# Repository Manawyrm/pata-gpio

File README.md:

pata-gpio
=============================

### Overview

**DISCLAIMER: This driver was developed for fun and learning ATA internals. If you're looking for a practical way to use PATA devices, look for commercial USB adapters.**  

pata-gpio is a Linux kernel driver for GPIO bitbanged PATA (also known as ATA/ATAPI or IDE).  
Pin configuration can be set via device tree, the regular ATA framework is used.  
  
IDE Primary/Secondary device support is implemented.  
  
### Performance

On a Raspberry Pi 4 (with direct GPIO) about **800 KiB/s reading, 500 KiB/s writing speed** is possible.
Most of the performance bottleneck is down to the usage of libgpiod (kernel gpio abstraction), 
which is optimized for tasks like switching LEDs. Data transmission is well outside the design scope of libgpiod. 
  
DMA and interrupts are not implemented at the moment.  
  
### Device tree configuration

Pin configuration can be specified in the device tree.  
An example device tree is provided as [atapi-direct.dts](https://github.com/Manawyrm/pata-gpio/blob/master/atapi-direct.dts).  
This includes the pin configuration for the schematic linked at the bottom of this readme.  
  
The following device tree properties are present:  

| Property      | Usage         | Required  |
| ------------- |-------------| -----|
| `databus-gpios`      | list of 16 GPIO pins, connected to ATA D0 - D15 in this order | yes |
| `cs-gpios`      | list of 2 GPIO pins, connected to ATA CS0 and CS1 in this order      | yes |
| `address-gpios` | list of 3 GPIO pins, connected to ATA DA0, DA1 and DA2 in this order  | yes |
| `strobe-write-gpio`      | GPIO pin, connected to ATA IOW line | yes |
| `strobe-read-gpio`      | GPIO pin, connected to ATA IOR line | yes |
| `reset-gpio` | GPIO pin, connected to ATA RESET line | no |

#### Interrupts

The driver has experimental interrupt support. An example configuration with GPIO interrupts is outlined in
`atapi-direct-irq.dts`.  
Interrupts are configured via the generic `interrupts` property. If the `interrupts` property is not specified
the driver falls back to polling.

### Compiling

Before loading (and running) the kernel module, make sure to load the device tree overlay.  
This can be done via the config.txt (on a Raspberry Pi): `dtoverlay=atapi-direct`, or by running `./loaddt.sh`.  
The latter script will also compile and save the device tree to `/boot/overlays/atapi-direct.dtbo`.  
  
This module needs kernel headers, regular build dependencies and a kernel with the config option `CONFIG_ATA_SFF=y` set.  
The `ATA_SFF` option is not the default on Raspberry Pis, so you will need to build a custom kernel.  

Compile the module using:   
`make`  

Load the module using:  
`insmod pata-gpio.ko`  
 
A helper script called `./run.sh` is provided, which will remove any loaded pata-gpio module, compile it and load the resulting module.  
Further status information can be shown by running `dmesg`. 

### Additional info

[Adapter PCB](https://github.com/Manawyrm/ATAPIHat-SMI)  
[Adapter schematic](https://github.com/Manawyrm/ATAPIHat-SMI/blob/master/gerbers/RevA/ATAPIHat-SMI/ATAPIHat-SMI.pdf)  

[Older schematic (not SMI-ready)](https://screenshot.tbspace.de/cmzhjfglbya.png)  
[Video: Audio CD streaming](https://www.youtube.com/watch?v=cHQhuzSn2oE)  
[Twitter: Project presentation](https://twitter.com/Manawyrm/status/1292084926980984833)  

### Credits
Thanks to [@Toble_Miner](https://github.com/TobleMiner) for a lot of help in the development of this driver!

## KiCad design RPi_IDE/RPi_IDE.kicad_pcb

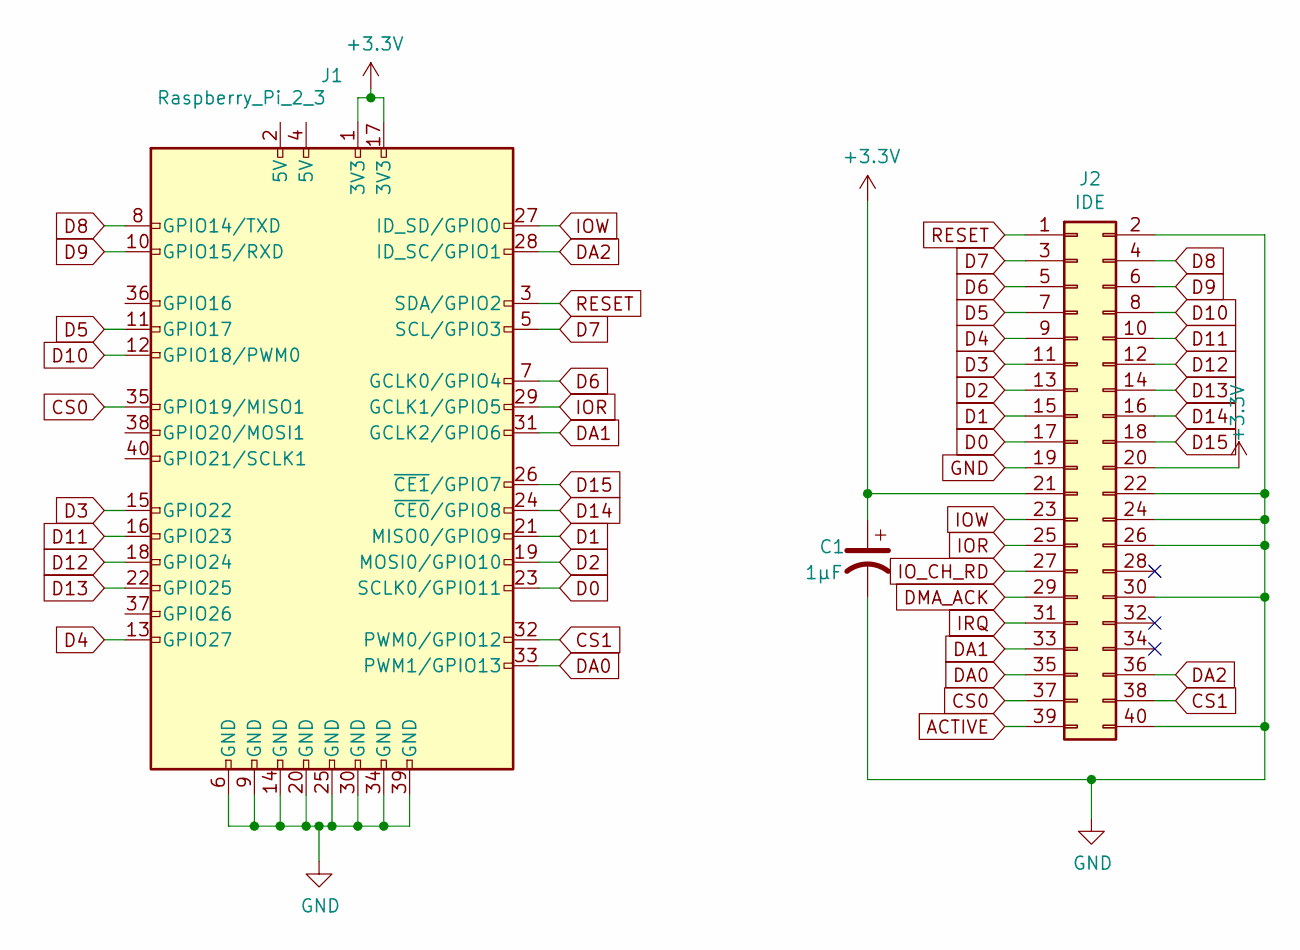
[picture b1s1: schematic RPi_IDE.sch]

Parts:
C1: 1µF; CP_Radial_D10.0mm_P5.00mm
J1: Raspberry_Pi_2_3; Pin_Header_Straight_2x20_Pitch2.54mm
J2: IDE; IDC-Header_2x20_P2.54mm_Latch_Vertical

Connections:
+3V3: C1.1, J1.1 (3V3), J1.17 (3V3), J2.20, J2.21
ACTIVE: J2.39
CS0: J1.35 (GPIO19/MISO1), J2.37
CS1: J1.32 (PWM0/GPIO12), J2.38
D0: J1.23 (SCLK0/GPIO11), J2.17
D1: J1.21 (MISO0/GPIO9), J2.15
D2: J1.19 (MOSI0/GPIO10), J2.13
D3: J1.15 (GPIO22), J2.11
D4: J1.13 (GPIO27), J2.9
D5: J1.11 (GPIO17), J2.7
D6: J1.7 (GCLK0/GPIO4), J2.5
D7: J1.5 (SCL/GPIO3), J2.3
D8: J1.8 (GPIO14/TXD), J2.4
D9: J1.10 (GPIO15/RXD), J2.6
D10: J1.12 (GPIO18/PWM0), J2.8
D11: J1.16 (GPIO23), J2.10
D12: J1.18 (GPIO24), J2.12
D13: J1.22 (GPIO25), J2.14
D14: J1.24 (~CE0~/GPIO8), J2.16
D15: J1.26 (~CE1~/GPIO7), J2.18
DA0: J1.33 (PWM1/GPIO13), J2.35
DA1: J1.31 (GCLK2/GPIO6), J2.33
DA2: J1.28 (ID_SC/GPIO1), J2.36
DMA_ACK: J2.29
GND: C1.2, J1.6 (GND), J1.9 (GND), J1.14 (GND), J1.20 (GND), J1.25 (GND), J1.30 (GND), J1.34 (GND), J1.39 (GND), J2.2, J2.19, J2.22, J2.24, J2.26, J2.30, J2.40
IOR: J1.29 (GCLK1/GPIO5), J2.25
IOW: J1.27 (ID_SD/GPIO0), J2.23
IO_CH_RD: J2.27
IRQ: J2.31
RESET: J1.3 (SDA/GPIO2), J2.1

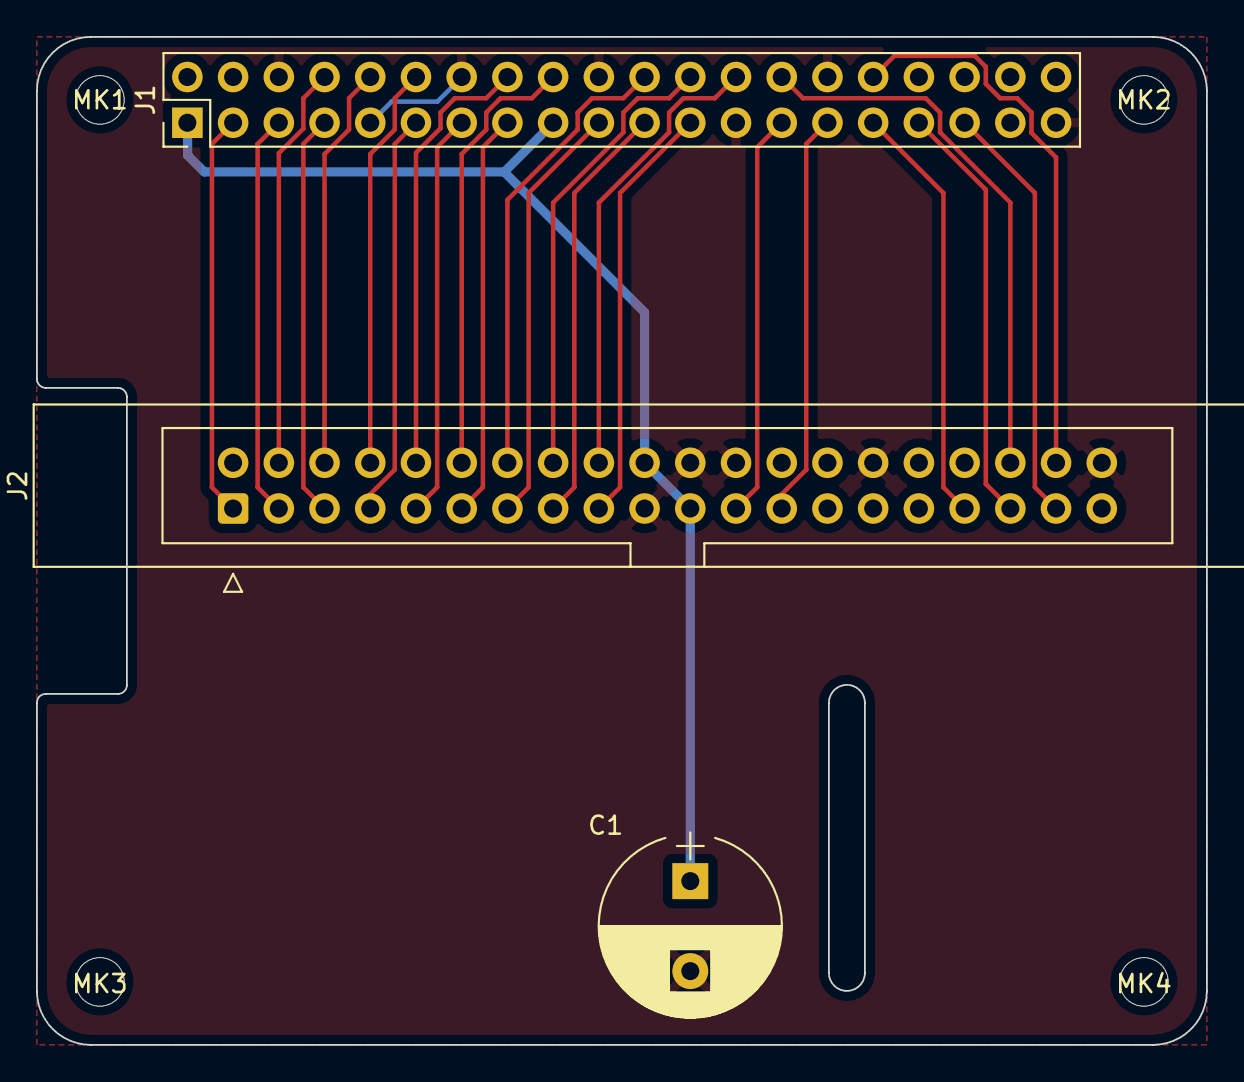
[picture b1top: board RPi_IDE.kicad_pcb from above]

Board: 2 copper layers, 65.0 x 56.0 mm, 7 parts (0 on the bottom side), 26 nets.

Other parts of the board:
MK1, MK2, MK3, MK4: M2.5; MountingHole_2.7mm_M2.5

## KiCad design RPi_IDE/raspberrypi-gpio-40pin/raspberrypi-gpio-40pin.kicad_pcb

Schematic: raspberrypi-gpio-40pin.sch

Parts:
MK1, MK2, MK3, MK4: M2.5; MountingHole_2.7mm_M2.5
P1: Conn_02x20_Odd_Even; PinSocket_2x20_P2.54mm_Vertical

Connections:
+3V3: P1.1, P1.17
+5V: P1.2, P1.4
/GPIO2(SDA1): P1.3
/GPIO3(SCL1): P1.5
/GPIO4(GCLK): P1.7
/GPIO5: P1.29
/GPIO6: P1.31
/GPIO7(SPI1_CE_N): P1.26
/GPIO8(SPI0_CE_N): P1.24
/GPIO9(SPI0_MISO): P1.21
/GPIO10(SPI0_MOSI): P1.19
/GPIO11(SPI0_SCK): P1.23
/GPIO12(PWM0): P1.32
/GPIO13(PWM1): P1.33
/GPIO14(TXD0): P1.8
/GPIO15(RXD0): P1.10
/GPIO16: P1.36
/GPIO17(GEN0): P1.11
/GPIO18(GEN1)(PWM0): P1.12
/GPIO19(SPI1_MISO): P1.35
/GPIO20(SPI1_MOSI): P1.38
/GPIO21(SPI1_SCK): P1.40
/GPIO22(GEN3): P1.15
/GPIO23(GEN4): P1.16
/GPIO24(GEN5): P1.18
/GPIO25(GEN6): P1.22
/GPIO26: P1.37
/GPIO27(GEN2): P1.13
/ID_SC: P1.28
/ID_SD: P1.27
GND: P1.6, P1.9, P1.14, P1.20, P1.25, P1.30, P1.34, P1.39

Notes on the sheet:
ID_SD and ID_SC PINS: These pins are reserved for HAT ID EEPROM. At boot time this I2C interface will be interrogated to look for an EEPROM that identifes the attached board and allows automagic setup of the GPIOs (and optionally, Linux drivers). DO NOT USE these pins for anything other than attach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
Mounting Holes

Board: 2 copper layers, 5 parts (1 on the bottom side), 3 nets, no tracks yet.

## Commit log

2020-08-02 add pata_gpio_read16 and pata_gpio_set_register
2020-08-02 fix cs line inversion
2020-08-02 add pata_gpio_write16() and temporary cf_identify()
2020-08-05 add taskfile read and load functions
2020-08-05 add PATA implementation
2020-08-07 Add slave support
2020-08-07 Add proper delays and fix code style
2020-08-08 Remove unused code
2020-08-08 Remove superfluous io direction setup and register write calls
    Increases performance by about 400%
2020-08-08 Add example device tree overlay
2020-08-08 Add readme
2020-08-08 Try to fix table formatting in readme
2020-08-08 Fix code formatting
2020-08-08 Add video to Readme
2020-08-10 Add experimental interrupt support
    This commit adds experimental interrupt support.
    During testing with flash-based CF cards in true IDE mode interrupt
    mode seems to be reliable and results in about 10 - 20% reduction in
    CPU utilization on a RPi4.
2020-08-10 Cleanup: replace ata port private data references by local variable
    Much more readable
2020-08-10 Don't shadow ndelay symbol
2020-08-10 Add safe timing mode via libata timing helpers
2020-08-11 Add GPL license
2020-08-12 KiCad PCB files
    Made a simple PCB for this circuit. IDC connector footprint and Raspberry Pi HAT template were both obtained on the official KiCad library repository on Github.
2020-08-12 Add link to Twitter and Adapter PCB
2020-08-12 Add link to new schematic
2020-08-12 add new device tree overlays for ATAPIHat-SMI
